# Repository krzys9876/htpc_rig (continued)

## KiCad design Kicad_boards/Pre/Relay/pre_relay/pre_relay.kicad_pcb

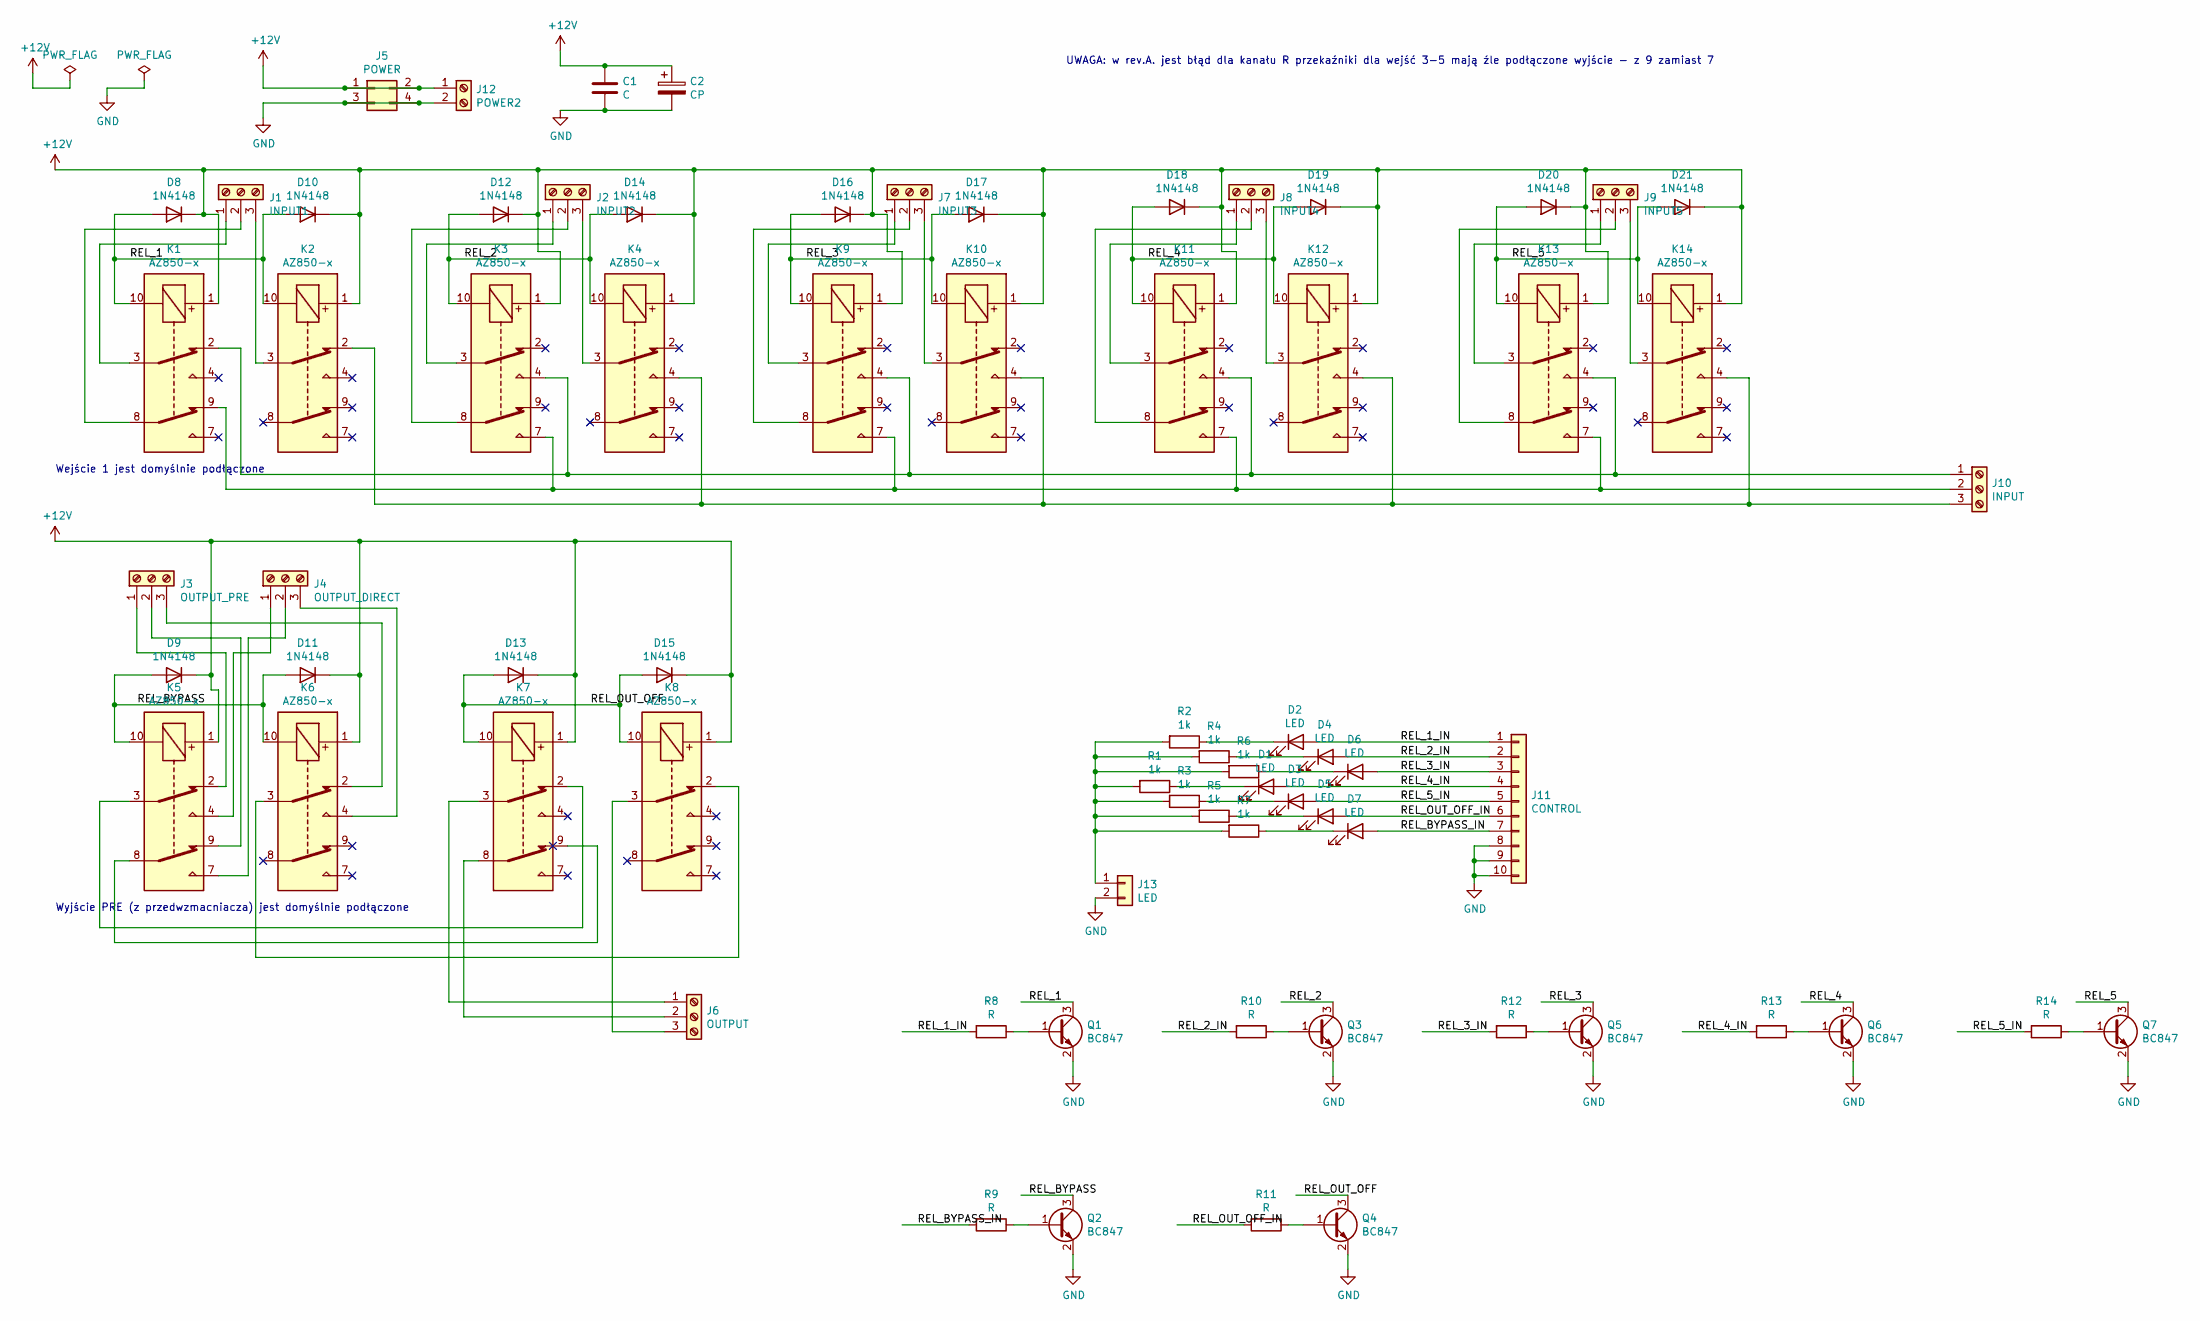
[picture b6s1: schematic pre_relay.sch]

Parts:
C1: C; C_1206_3216Metric
C2: CP; C_1210_3225Metric
D1, D2, D3, D4, D5, D6, D7: LED; LED_0805_2012Metric
D8, D9, D10, D11, D12, D13, D14, D15, D16, D17, D18, D19, D20, D21: 1N4148; D_DO-35_SOD27_P7.62mm_Horizontal
J1: INPUT1; TerminalBlock_RND_205-00002_1x03_P5.00mm_Horizontal
J2: INPUT2; TerminalBlock_RND_205-00002_1x03_P5.00mm_Horizontal
J3: OUTPUT_PRE; TerminalBlock_RND_205-00002_1x03_P5.00mm_Horizontal
J4: OUTPUT_DIRECT; TerminalBlock_RND_205-00002_1x03_P5.00mm_Horizontal
J5: POWER; PinHeader_2x02_P2.54mm_Vertical
J6: OUTPUT; TerminalBlock_RND_205-00002_1x03_P5.00mm_Horizontal
J7: INPUT3; TerminalBlock_RND_205-00002_1x03_P5.00mm_Horizontal
J8: INPUT4; TerminalBlock_RND_205-00002_1x03_P5.00mm_Horizontal
J9: INPUT5; TerminalBlock_RND_205-00002_1x03_P5.00mm_Horizontal
J10: INPUT; TerminalBlock_RND_205-00002_1x03_P5.00mm_Horizontal
J11: CONTROL; IDC-Header_2x05_P2.54mm_Vertical
J12: POWER2; TerminalBlock_RND_205-00001_1x02_P5.00mm_Horizontal
J13: LED; PinHeader_1x02_P2.54mm_Vertical
K1, K2, K3, K4, K5, K6, K7, K8, K9, K10, K11, K12, K13, K14: AZ850-x; Relay_DPDT_FRT5
Q1, Q2, Q3, Q4, Q5, Q6, Q7: BC847; SOT-23
R1, R2, R3, R4, R5, R6, R7: 1k; R_0805_2012Metric
R8, R9, R10, R11, R12, R13, R14: R; R_0805_2012Metric

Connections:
+12V: C1.1, C2.1, D8.1 (K), D9.1 (K), D10.1 (K), D11.1 (K), D12.1 (K), D13.1 (K), D14.1 (K), D15.1 (K), D16.1 (K), D17.1 (K), D18.1 (K), D19.1 (K), D20.1 (K), D21.1 (K), J5.1, J5.2, J12.1, K1.1, K2.1, K3.1, K4.1, K5.1, K6.1, K7.1, K8.1, K9.1, K10.1, K11.1, K12.1, K13.1, K14.1
/REL_1: D8.2 (A), D10.2 (A), K1.10, K2.10, Q1.3 (C)
/REL_1_IN: D2.2 (A), J11.1, R8.2
/REL_2: D12.2 (A), D14.2 (A), K3.10, K4.10, Q3.3 (C)
/REL_2_IN: D4.2 (A), J11.2, R10.2
/REL_3: D16.2 (A), D17.2 (A), K9.10, K10.10, Q5.3 (C)
/REL_3_IN: D6.2 (A), J11.3, R12.2
/REL_4: D18.2 (A), D19.2 (A), K11.10, K12.10, Q6.3 (C)
/REL_4_IN: D1.2 (A), J11.4, R13.2
/REL_5: D20.2 (A), D21.2 (A), K13.10, K14.10, Q7.3 (C)
/REL_5_IN: D3.2 (A), J11.5, R14.2
/REL_BYPASS: D9.2 (A), D11.2 (A), K5.10, K6.10, Q2.3 (C)
/REL_BYPASS_IN: D7.2 (A), J11.7, R9.2
/REL_OUT_OFF: D13.2 (A), D15.2 (A), K7.10, K8.10, Q4.3 (C)
/REL_OUT_OFF_IN: D5.2 (A), J11.6, R11.2
GND: C1.2, C2.2, J5.3, J5.4, J11.8, J11.9, J11.10, J12.2, J13.2, Q1.2 (E), Q2.2 (E), Q3.2 (E), Q4.2 (E), Q5.2 (E), Q6.2 (E), Q7.2 (E)
unnamed: D1.1 (K), R1.1
unnamed: D2.1 (K), R2.1
unnamed: D3.1 (K), R3.1
unnamed: D4.1 (K), R4.1
unnamed: D5.1 (K), R5.1
unnamed: D6.1 (K), R6.1
unnamed: D7.1 (K), R7.1
unnamed: J1.1, K1.3
unnamed: J1.2, K1.8
unnamed: J1.3, K2.3
unnamed: J2.1, K3.3
unnamed: J2.2, K3.8
unnamed: J2.3, K4.3
unnamed: J3.1, K5.2
unnamed: J3.2, K5.9
unnamed: J3.3, K6.2
unnamed: J4.1, K5.4
unnamed: J4.2, K5.7
unnamed: J4.3, K6.4
unnamed: J6.1, K7.3
unnamed: J6.2, K7.8
unnamed: J6.3, K8.3
unnamed: J7.1, K9.3
unnamed: J7.2, K9.8
unnamed: J7.3, K10.3
unnamed: J8.1, K11.3
unnamed: J8.2, K11.8
unnamed: J8.3, K12.3
unnamed: J9.1, K13.3
unnamed: J9.2, K13.8
unnamed: J9.3, K14.3
unnamed: J10.1, K1.2, K3.4, K9.4, K11.4, K13.4
unnamed: J10.2, K1.9, K3.7, K9.7, K11.7, K13.7
unnamed: J10.3, K2.2, K4.4, K10.4, K12.4, K14.4
unnamed: J13.1, R1.2, R2.2, R3.2, R4.2, R5.2, R6.2, R7.2
unnamed: K5.3, K7.2
unnamed: K5.8, K7.9
unnamed: K6.3, K8.2
unnamed: Q1.1 (B), R8.1
unnamed: Q2.1 (B), R9.1
unnamed: Q3.1 (B), R10.1
unnamed: Q4.1 (B), R11.1
unnamed: Q5.1 (B), R12.1
unnamed: Q6.1 (B), R13.1
unnamed: Q7.1 (B), R14.1

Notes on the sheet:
Wejście 1 jest domyślnie podłączone
Wyjście PRE (z przedwzmacniacza) jest domyślnie podłączone
UWAGA: w rev.A. jest błąd dla kanału R przekaźniki dla wejść 3-5 mają źle podłączone wyjście - z 9 zamiast 7

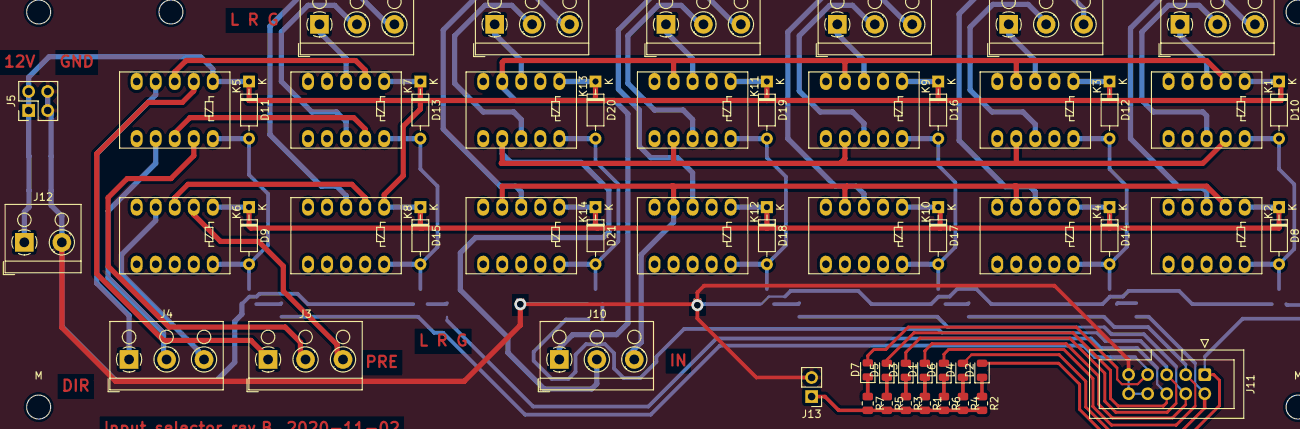
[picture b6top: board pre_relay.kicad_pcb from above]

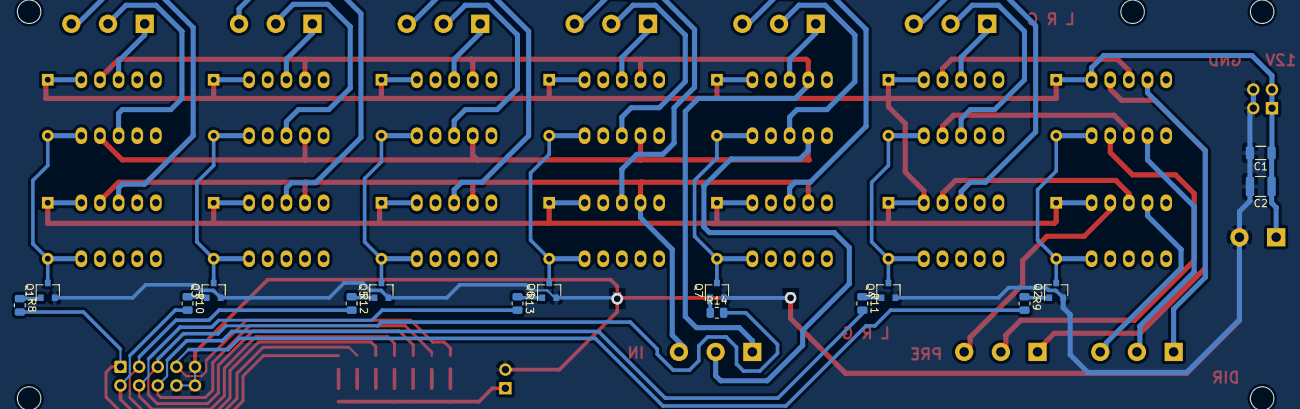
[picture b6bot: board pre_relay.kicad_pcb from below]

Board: 2 copper layers, 76 parts (16 on the bottom side), 61 nets.

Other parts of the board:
M: M3; MountingHole_3.2mm_M3
M#2, M#3, M#4, M#5: M3; MountingHole_3.2mm_M3

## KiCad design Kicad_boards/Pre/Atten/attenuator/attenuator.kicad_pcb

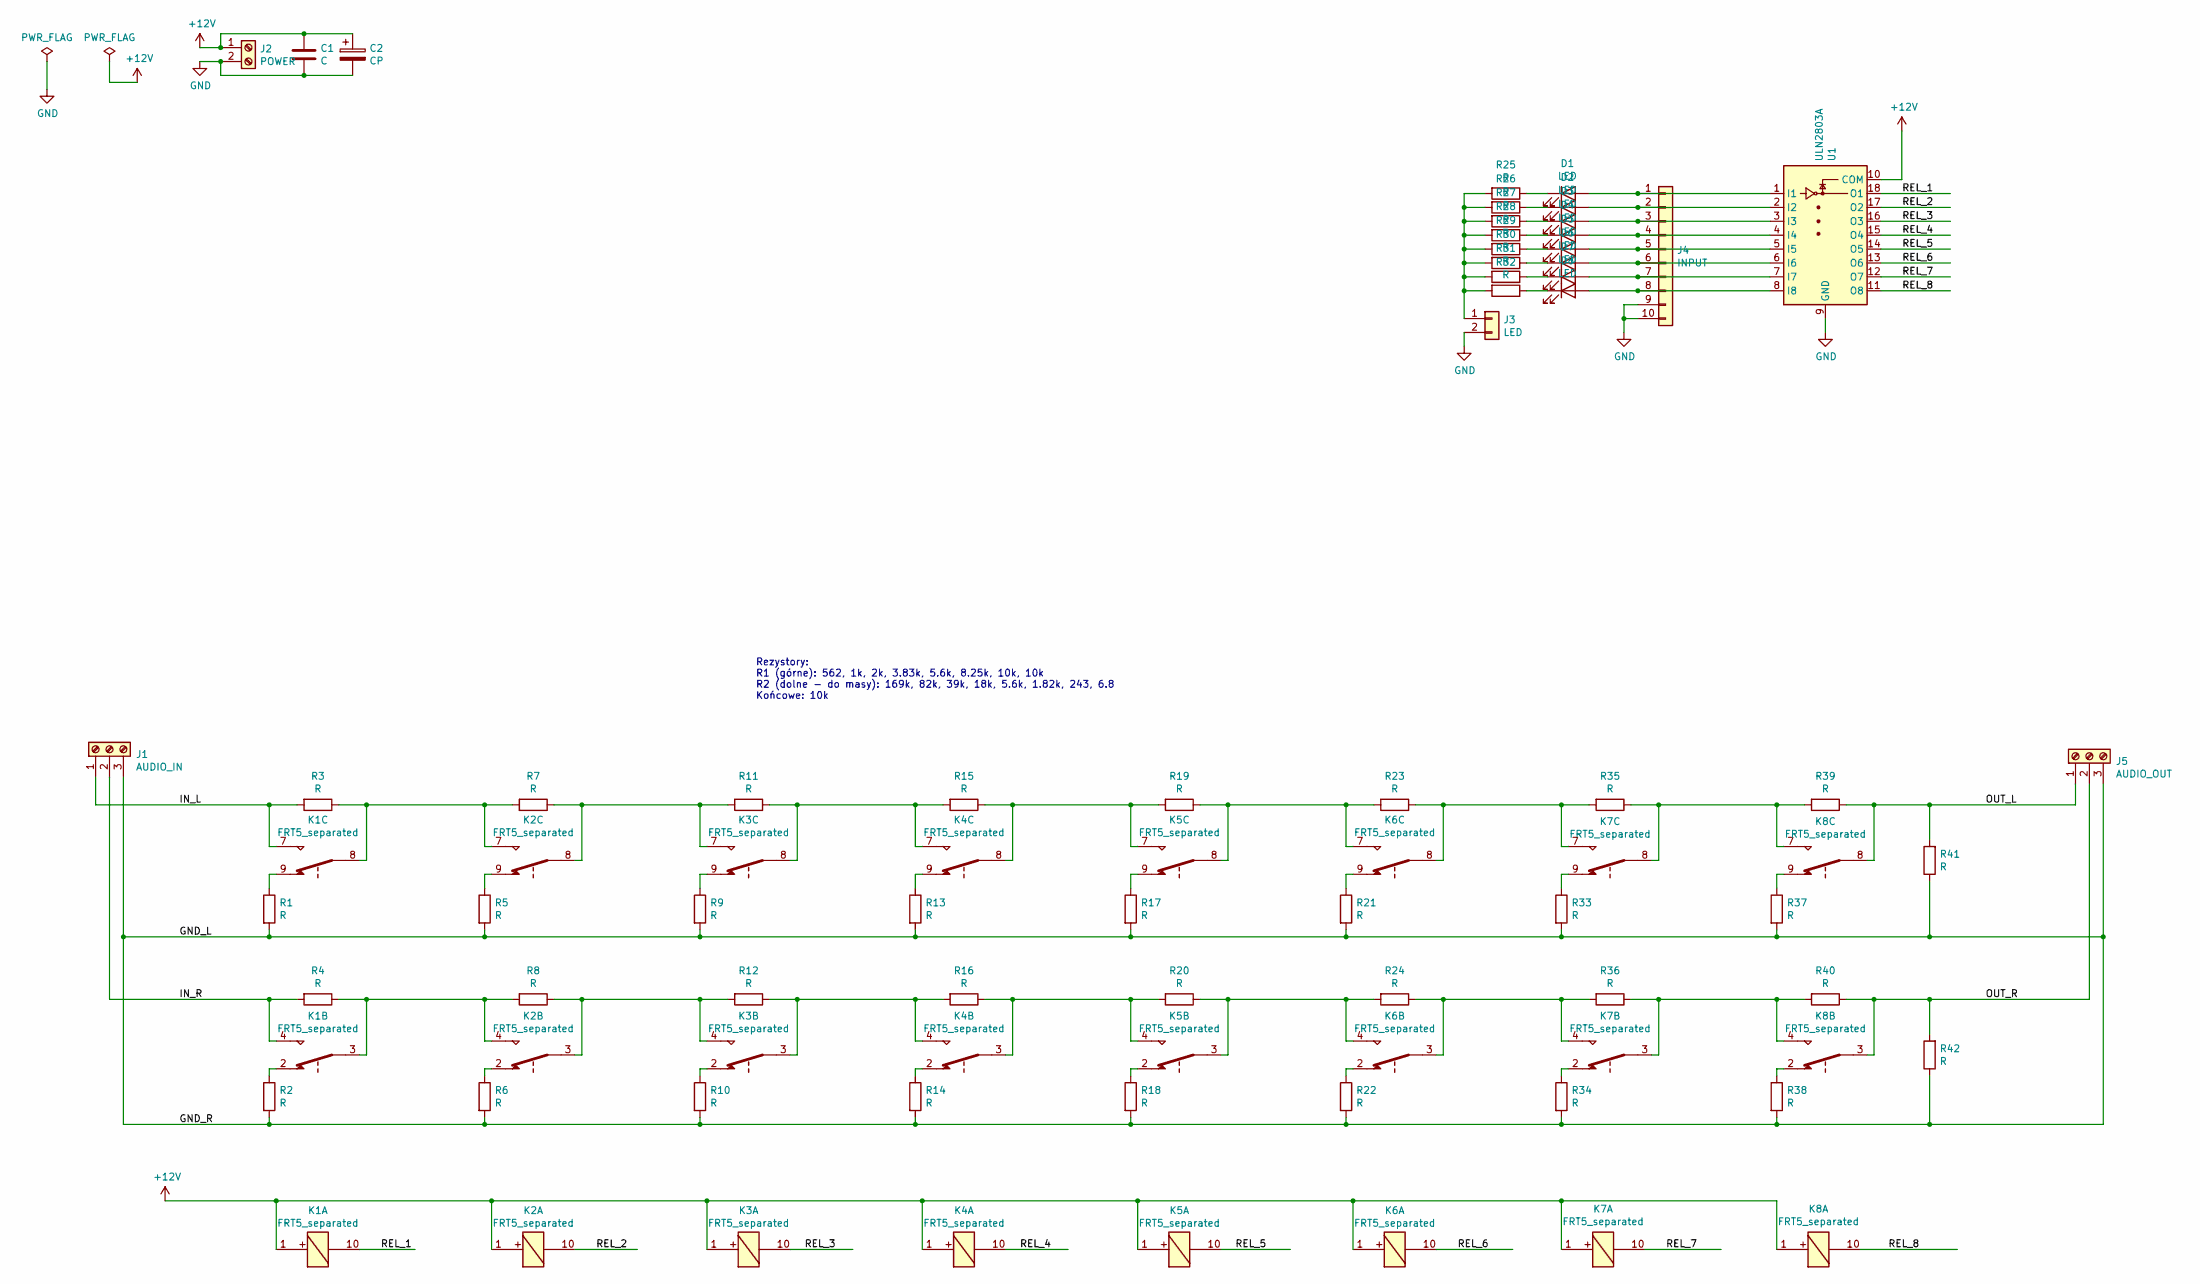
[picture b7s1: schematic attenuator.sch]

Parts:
C1: C; C_1206_3216Metric
C2: CP; C_1210_3225Metric
D1, D2, D3, D4, D5, D6, D7, D8: LED; LED_0805_2012Metric
J1: AUDIO_IN; TerminalBlock_RND_205-00013_1x03_P5.00mm_Horizontal
J2: POWER; TerminalBlock_RND_205-00012_1x02_P5.00mm_Horizontal
J3: LED; PinHeader_1x02_P2.54mm_Vertical
J4: INPUT; IDC-Header_2x05_P2.54mm_Vertical
J5: AUDIO_OUT; TerminalBlock_RND_205-00013_1x03_P5.00mm_Horizontal
K1, K2, K3, K4, K5, K6, K7, K8: FRT5_separated; Relay_DPDT_FRT5
R1, R2, R3, R4, R5, R6, R7, R8, R9, R10, R11, R12, R13, R14, R15, R16, R17, R18, R19, R20, R21, R22, R23, R24, R33, R34, R35, R36, R37, R38, R39, R40, R41, R42: R; R_Axial_DIN0207_L6.3mm_D2.5mm_P10.16mm_Horizontal
R25, R26, R27, R28, R29, R30, R31, R32: R; R_0805_2012Metric
U1: ULN2803A; DIP-18_W7.62mm

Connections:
+12V: C1.1, C2.1, J2.1, K1.1, K2.1, K3.1, K4.1, K5.1, K6.1, K7.1, K8.1, U1.10 (COM)
/GND_L: J1.3, J5.3, R1.2, R2.2, R5.2, R6.2, R9.2, R10.2, R13.2, R14.2, R17.2, R18.2, R21.2, R22.2, R33.2, R34.2, R37.2, R38.2, R41.1, R42.1
/IN_L: J1.1, K1.7, R3.2
/IN_R: J1.2, K1.4, R4.2
/OUT_L: J5.1, K8.8, R39.1, R41.2
/OUT_R: J5.2, K8.3, R40.1, R42.2
/REL_1: K1.10, U1.18 (O1)
/REL_2: K2.10, U1.17 (O2)
/REL_3: K3.10, U1.16 (O3)
/REL_4: K4.10, U1.15 (O4)
/REL_5: K5.10, U1.14 (O5)
/REL_6: K6.10, U1.13 (O6)
/REL_7: K7.10, U1.12 (O7)
/REL_8: K8.10, U1.11 (O8)
GND: C1.2, C2.2, J2.2, J3.2, J4.9, J4.10, U1.9 (GND)
unnamed: D1.1 (K), R25.1
unnamed: D1.2 (A), J4.1, U1.1 (I1)
unnamed: D2.1 (K), R26.1
unnamed: D2.2 (A), J4.2, U1.2 (I2)
unnamed: D3.1 (K), R27.1
unnamed: D3.2 (A), J4.3, U1.3 (I3)
unnamed: D4.1 (K), R28.1
unnamed: D4.2 (A), J4.4, U1.4 (I4)
unnamed: D5.1 (K), R29.1
unnamed: D5.2 (A), J4.5, U1.5 (I5)
unnamed: D6.1 (K), R30.1
unnamed: D6.2 (A), J4.6, U1.6 (I6)
unnamed: D7.1 (K), R31.1
unnamed: D7.2 (A), J4.7, U1.7 (I7)
unnamed: D8.1 (K), R32.1
unnamed: D8.2 (A), J4.8, U1.8 (I8)
unnamed: J3.1, R25.2, R26.2, R27.2, R28.2, R29.2, R30.2, R31.2, R32.2
unnamed: K1.2, R2.1
unnamed: K1.3, K2.4, R4.1, R8.2
unnamed: K1.8, K2.7, R3.1, R7.2
unnamed: K1.9, R1.1
unnamed: K2.2, R6.1
unnamed: K2.3, K3.4, R8.1, R12.2
unnamed: K2.8, K3.7, R7.1, R11.2
unnamed: K2.9, R5.1
unnamed: K3.2, R10.1
unnamed: K3.3, K4.4, R12.1, R16.2
unnamed: K3.8, K4.7, R11.1, R15.2
unnamed: K3.9, R9.1
unnamed: K4.2, R14.1
unnamed: K4.3, K5.4, R16.1, R20.2
unnamed: K4.8, K5.7, R15.1, R19.2
unnamed: K4.9, R13.1
unnamed: K5.2, R18.1
unnamed: K5.3, K6.4, R20.1, R24.2
unnamed: K5.8, K6.7, R19.1, R23.2
unnamed: K5.9, R17.1
unnamed: K6.2, R22.1
unnamed: K6.3, K7.4, R24.1, R36.2
unnamed: K6.8, K7.7, R23.1, R35.2
unnamed: K6.9, R21.1
unnamed: K7.2, R34.1
unnamed: K7.3, K8.4, R36.1, R40.2
unnamed: K7.8, K8.7, R35.1, R39.2
unnamed: K7.9, R33.1
unnamed: K8.2, R38.1
unnamed: K8.9, R37.1

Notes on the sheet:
Rezystory: R1 (górne): 562, 1k, 2k, 3.83k, 5.6k, 8.25k, 10k, 10k R2 (dolne - do masy): 169k, 82k, 39k, 18k, 5.6k, 1.82k, 243, 6.8 Końcowe: 10k

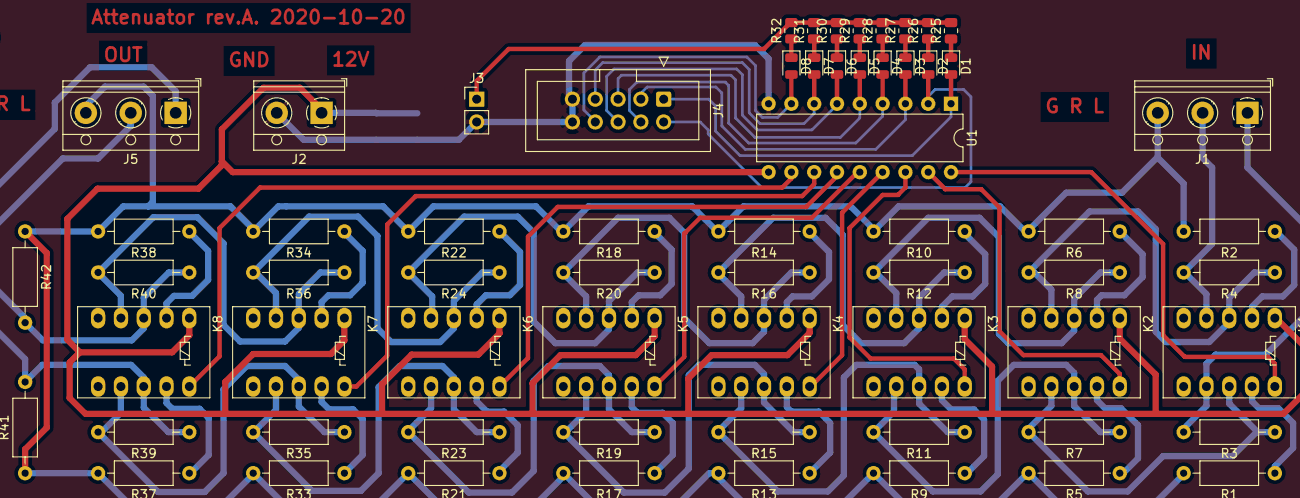
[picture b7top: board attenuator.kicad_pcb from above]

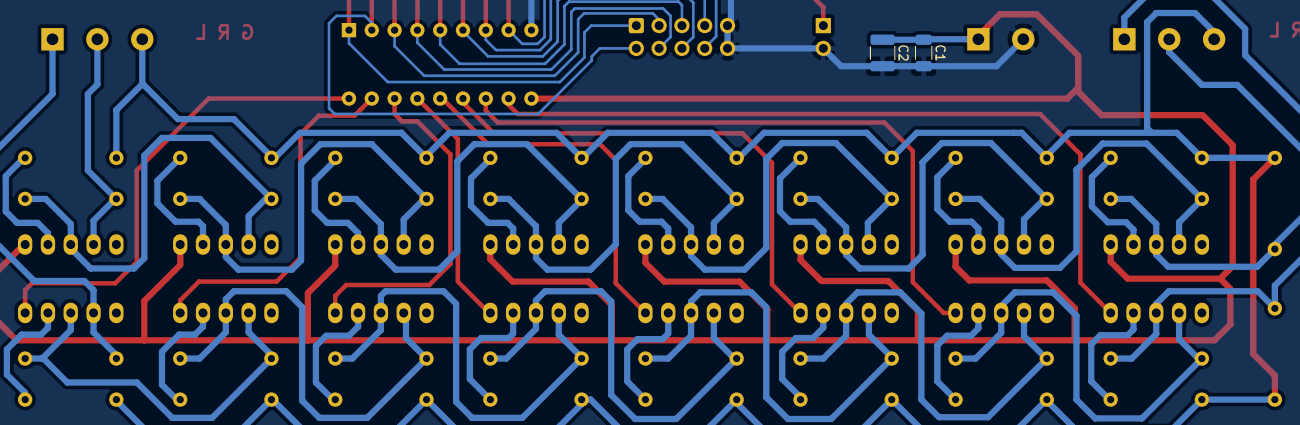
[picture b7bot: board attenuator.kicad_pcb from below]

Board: 2 copper layers, 70 parts (2 on the bottom side), 62 nets.

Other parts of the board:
M: M3; MountingHole_3.2mm_M3
M#2, M#3, M#4: M3; MountingHole_3.2mm_M3

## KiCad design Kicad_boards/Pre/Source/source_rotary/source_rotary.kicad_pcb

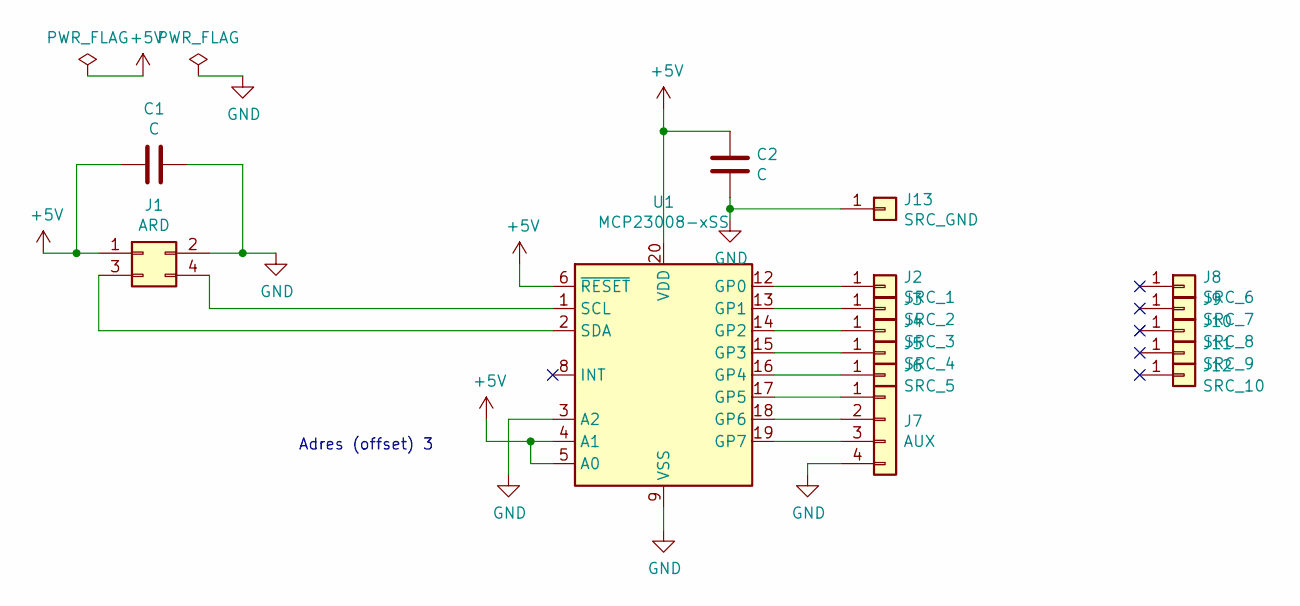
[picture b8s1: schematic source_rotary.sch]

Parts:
C1, C2: C; C_1206_3216Metric
J1: ARD; PinHeader_2x02_P2.54mm_Vertical_SMD
J2: SRC_1; PinHeader_1x01_P1.00mm_Vertical
J3: SRC_2; PinHeader_1x01_P1.00mm_Vertical
J4: SRC_3; PinHeader_1x01_P1.00mm_Vertical
J5: SRC_4; PinHeader_1x01_P1.00mm_Vertical
J6: SRC_5; PinHeader_1x01_P1.00mm_Vertical
J7: AUX; PinHeader_2x02_P2.54mm_Vertical_SMD
J8: SRC_6; PinHeader_1x01_P1.00mm_Vertical
J9: SRC_7; PinHeader_1x01_P1.00mm_Vertical
J10: SRC_8; PinHeader_1x01_P1.00mm_Vertical
J11: SRC_9; PinHeader_1x01_P1.00mm_Vertical
J12: SRC_10; PinHeader_1x01_P1.00mm_Vertical
J13: SRC_GND; PinHeader_1x01_P1.00mm_Vertical
U1: MCP23008-xSS; SSOP-20_5.3x7.2mm_P0.65mm

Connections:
+5V: C1.1, C2.1, J1.1, U1.4 (A1), U1.5 (A0), U1.6 (~RESET), U1.20 (VDD)
GND: C1.2, C2.2, J1.2, J7.4, J13.1, U1.3 (A2), U1.9 (VSS)
unnamed: J1.3, U1.2 (SDA)
unnamed: J1.4, U1.1 (SCL)
unnamed: J2.1, U1.12 (GP0)
unnamed: J3.1, U1.13 (GP1)
unnamed: J4.1, U1.14 (GP2)
unnamed: J5.1, U1.15 (GP3)
unnamed: J6.1, U1.16 (GP4)
unnamed: J7.1, U1.17 (GP5)
unnamed: J7.2, U1.18 (GP6)
unnamed: J7.3, U1.19 (GP7)

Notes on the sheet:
Adres (offset) 3

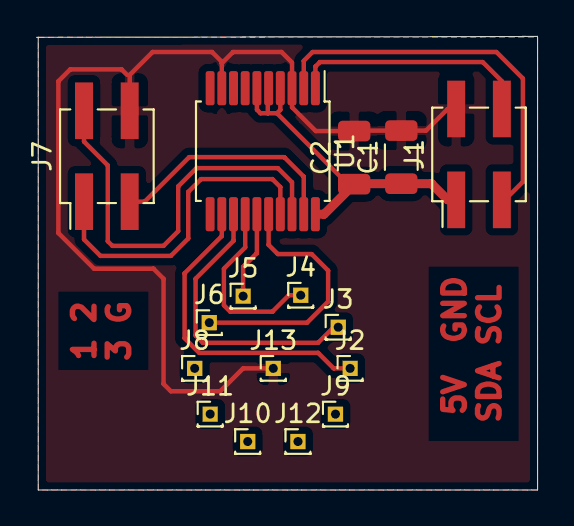
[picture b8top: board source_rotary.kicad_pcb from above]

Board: 2 copper layers, 27.8 x 25.2 mm, 16 parts (0 on the bottom side), 12 nets.

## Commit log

2023-11-06 download album art as file to enable proper downloading at pi startup
2023-11-06 revert, keep standard album art retrieval as http get
2023-11-13 add CD Audio playback
